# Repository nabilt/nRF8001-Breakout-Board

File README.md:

nRF8001-Breakout-Board
==========================================

* Author:    Nabil Tewolde (<nabil.tewolde@gmail.com>)
* Version:   0.9
* Website:   <http://www.nabiltewolde.com>
* GitHub:    <https://github.com/nabilt/nRF8001-Breakout-Board>

This hardware project is the reference schematic for the [nRF8001] Bluetooth Low Energy chip redone in Eagle. It is currently untested. The goal of this project is to develop a low power, cheap, cross-platform wireless module for wireless projects. I plan to include open firmware and demos for iOS and Android. Checkout my [blog post] for more info.

[nRF8001]: http://www.nordicsemi.com/eng/Products/Bluetooth-R-low-energy/nRF8001
[blog post]: https://nabil.me/2012/04/09/open-source-bluetooth-4-breakout-board-means-no-more-mi-fi/
Why nRF8001 and not another [Bluetooth 4 chip]?

* Publicly available datasheet
* Simple circuitry, few passives and no integrated uC
* Cheap, $4.98 CAD on [Mouser]
* Small, currently the board is 1’’ x 0.9’’

[Bluetooth 4 chip]: http://developer.bluetooth.org/DevelopmentResources/DevelopmentPlatforms/Pages/Development-Platforms.aspx
[Mouser]: http://ca.mouser.com/ProductDetail/Nordic-Semiconductor/nRF8001-R2Q32-T/?qs=yd0qOhnSiDfAxQAlSXMVEQ%3d%3d

Interesting Bluetooth 4 facts:

* Runs for years on a coin cell battery
* Works over a wide range; 10 to 100 meters
* 1Mbps over the air data rate; 0.2 Mbps throughput 
* Virtually all new devices made in 2012 will contain Bluetooth 4 
* Apple only provides a free API for Bluetooth 4 accessories

Checkout <http://www.bluetooth.com/Pages/Bluetooth-Smart-Devices.aspx> for a list of Bluetooth 4 compatible devices.

Licensing
---------

nRF8001-Breakout-Board by Nabil Tewolde is licensed under a Creative Commons Attribution-ShareAlike 3.0 Unported License.

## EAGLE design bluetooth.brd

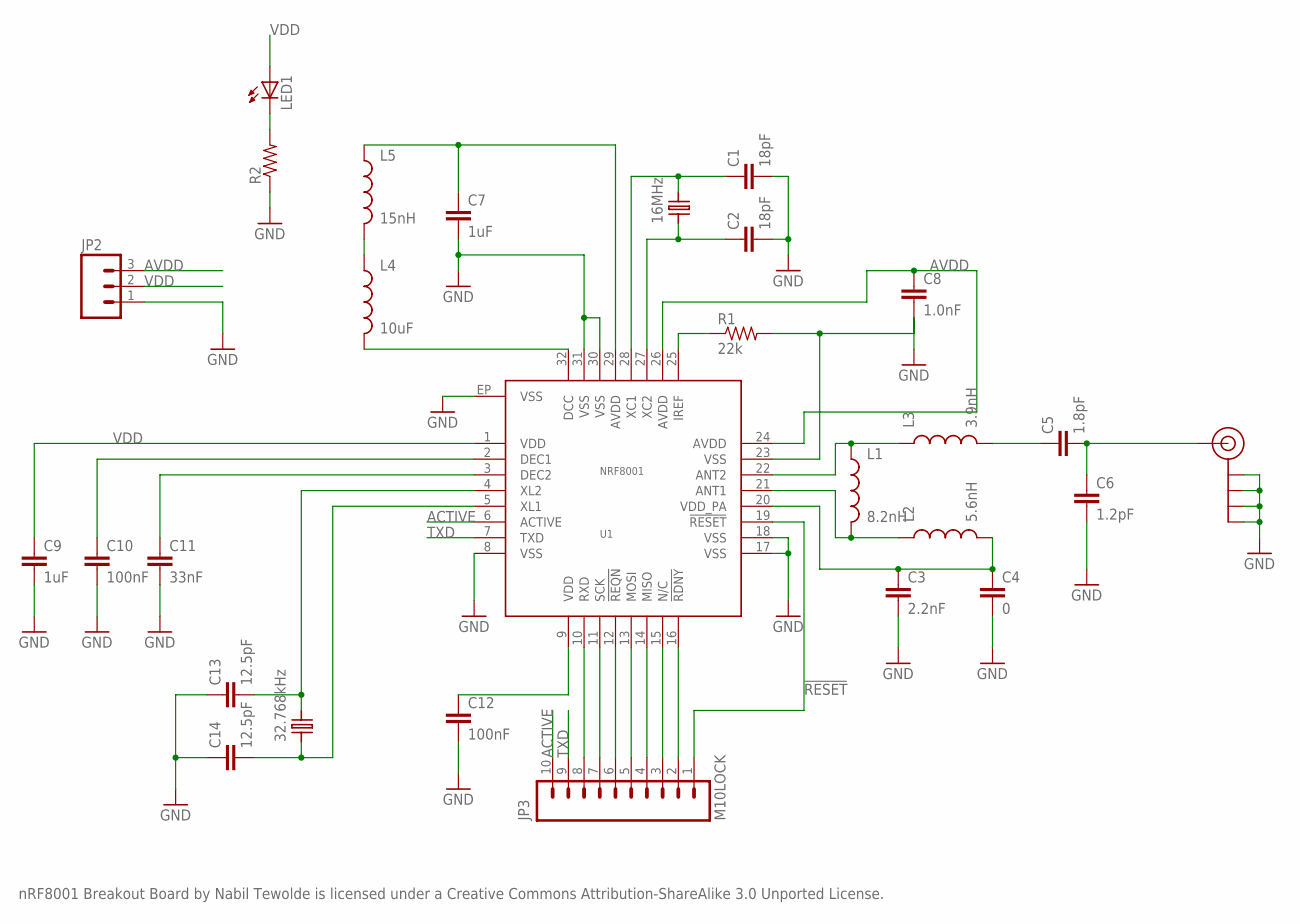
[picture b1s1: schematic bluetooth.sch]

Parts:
C1, C2: 18pF; 0603-CAP
C3: 2.2nF; 0603-CAP
C4: 0; 0603-CAP
C5: 1.8pF; 0603-CAP
C6: 1.2pF; 0603-CAP
C7, C9: 1uF; 0603-CAP
C8: 1.0nF; 0603-CAP
C10, C12: 100nF; 0603-CAP
C11: 33nF; 0603-CAP
C13, C14: 12.5pF; 0603-CAP
J$1: SMA_EDGE; SMA-EDGE
JP2: M03LOCK; 1X03_LOCK
JP3: M10LOCK; 1X10_LOCK
L1: 8.2nH; 0603
L2: 5.6nH; 0603
L3: 3.9nH; 0603
L4: 10uF; 0603
L5: 15nH; 0603
LED1: LED0603; LED-0603
R1: 22k; 0603-RES
R2: RESISTOR0603-RES; 0603-RES
U1: NRF8001; QFN-32
X1: 16MHz; CRYSTAL-2.5X3.5
X2: 32.768kHz; CRYSTAL-ABS10

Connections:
!RESET: JP3.1, U1.19 (!RESET)
ACTIVE: JP3.10, U1.6 (ACTIVE)
AVDD: C8.1, JP2.3, U1.24 (AVDD), U1.26 (AVDD)
GND: C1.2, C2.2, C3.2, C4.2, C6.2, C7.2, C8.2, C9.2, C10.2, C11.2, C12.2, C13.1, C14.1, J$1.GND@0 (GND), J$1.GND@1 (GND), J$1.GND@2 (GND), J$1.GND@3 (GND), JP2.1, R1.2, R2.1, U1.8 (VSS), U1.17 (VSS), U1.18 (VSS), U1.23 (VSS), U1.30 (VSS), U1.31 (VSS), U1.EP (VSS)
unnamed: L4.1, L5.2
unnamed: L4.2, U1.32 (DCC)
unnamed: L1.1, L3.1, U1.22 (ANT2)
unnamed: C7.1, L5.1, U1.29 (AVDD)
unnamed: LED1.C, R2.2
unnamed: C10.1, U1.2 (DEC1)
unnamed: C11.1, U1.3 (DEC2)
unnamed: L1.2, L2.1, U1.21 (ANT1)
unnamed: C5.1, L3.2
unnamed: C5.2, C6.1, J$1.SIG (SIGNAL)
unnamed: R1.1, U1.25 (IREF)
unnamed: C3.1, C4.1, L2.2, U1.20 (VDD_PA)
unnamed: C2.1, U1.27 (XC2), X1.P$1
unnamed: C1.1, U1.28 (XC1), X1.P$3
unnamed: C13.2, U1.4 (XL2), X2.P$2
unnamed: C14.2, U1.5 (XL1), X2.P$1
unnamed: JP3.2, U1.16 (!RDNY)
unnamed: JP3.3, U1.15 (N/C)
unnamed: JP3.4, U1.14 (MISO)
unnamed: JP3.5, U1.13 (MOSI)
unnamed: JP3.6, U1.12 (!REQN)
unnamed: JP3.7, U1.11 (SCK)
unnamed: JP3.8, U1.10 (RXD)
TXD: JP3.9, U1.7 (TXD)
VDD: C9.1, C12.1, JP2.2, LED1.A, U1.1 (VDD), U1.9 (VDD)

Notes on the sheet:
nRF8001 Breakout Board by Nabil Tewolde is licensed under a Creative Commons Attribution-ShareAlike 3.0 Unported License.

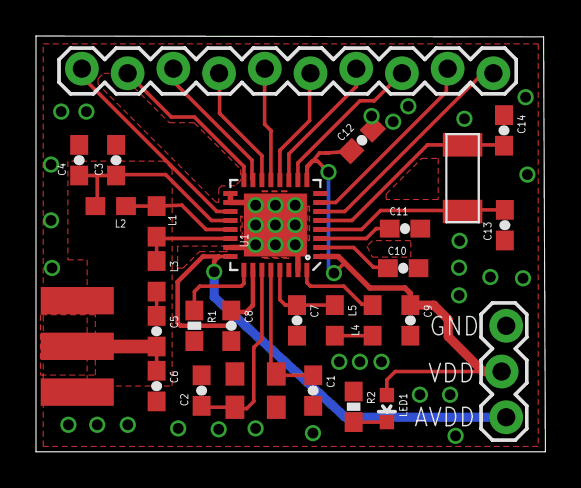
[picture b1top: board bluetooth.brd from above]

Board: 2 copper layers, 28.3 x 23.1 mm, 28 parts (0 on the bottom side), 29 nets.

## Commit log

2012-04-09 fix readme
2012-04-20 updated BOM, fixed 32kHz crystal footprint and added datasheet
2012-04-20 small DRC fix, added gerber files
2013-01-07 Connected pin 9 (power) to VDD. Oops

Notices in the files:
bluetooth.brd:
CC-BY-SA
parts and their libraries:
SparkFun: Licensing: CC v3.0 Share-Alike You are welcome to use this library for commercial purposes.
